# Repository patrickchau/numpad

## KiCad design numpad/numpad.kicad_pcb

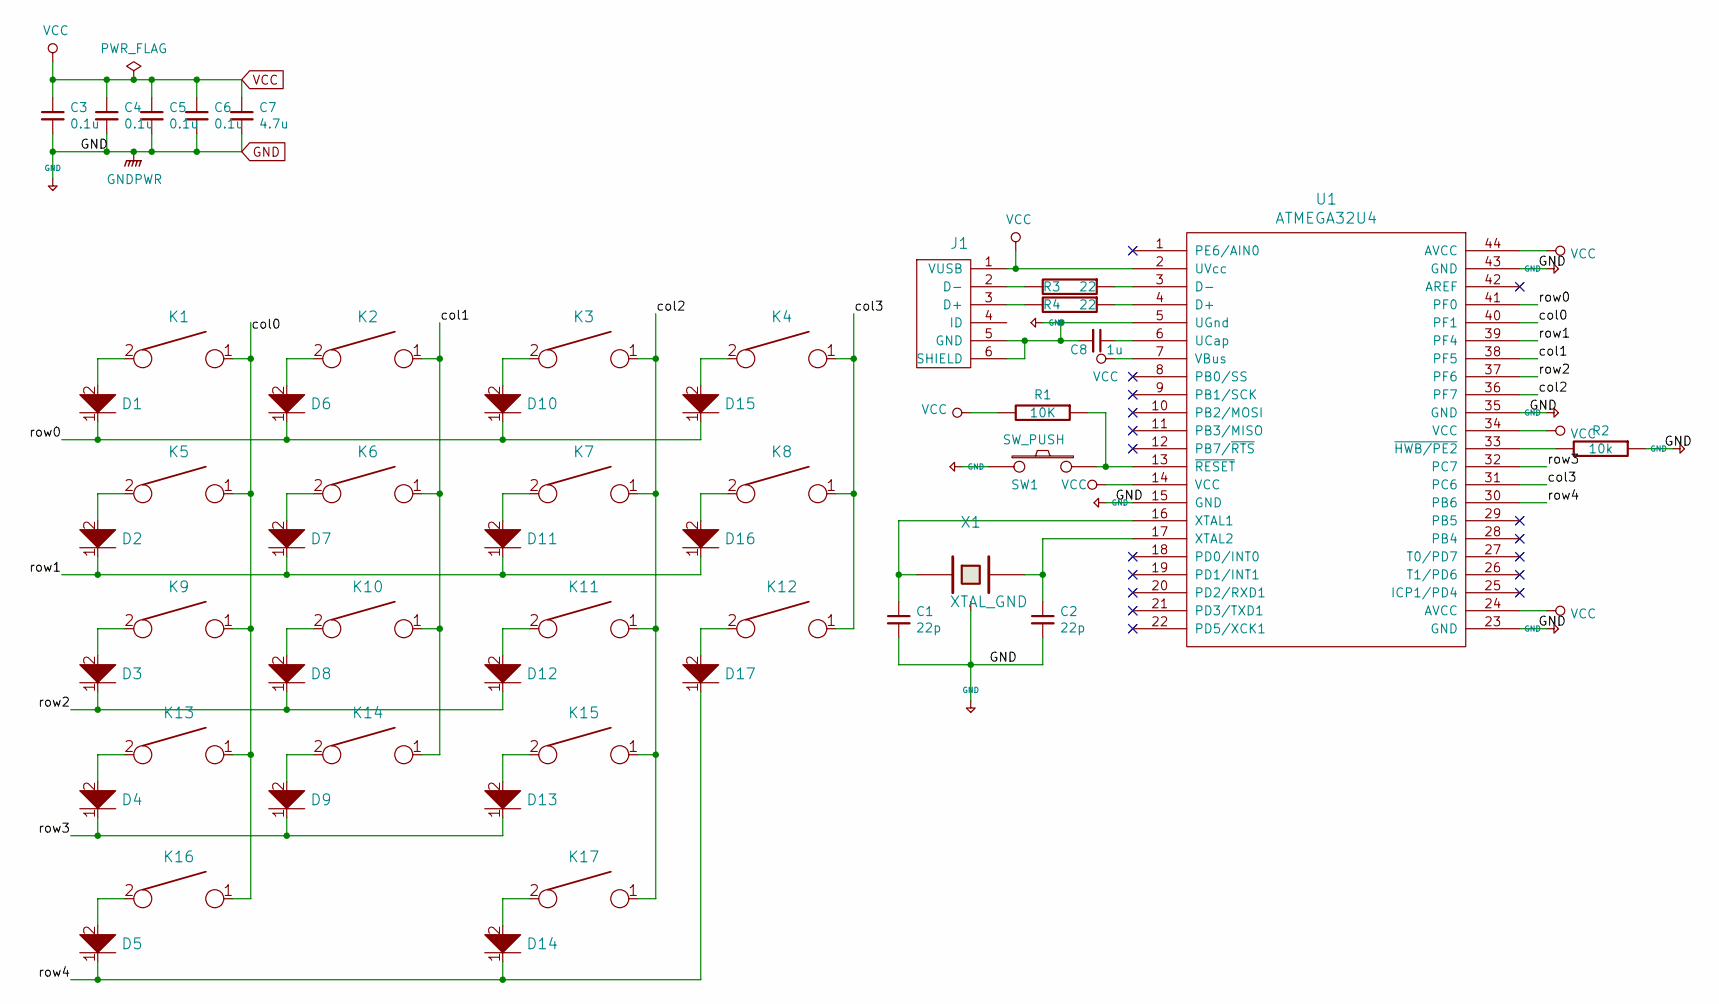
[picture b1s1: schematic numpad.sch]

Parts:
C1, C2: 22p; C_0805_2012Metric_Pad1.15x1.40mm_HandSolder
C3, C4, C5, C6: 0.1u; C_0805_2012Metric_Pad1.15x1.40mm_HandSolder
C7: 4.7u; C_0805_2012Metric_Pad1.15x1.40mm_HandSolder
C8: 1u; C_0805_2012Metric_Pad1.15x1.40mm_HandSolder
D1, D2, D3, D4, D5, D6, D7, D8, D9, D10, D11, D12, D13, D14, D15, D16, D17: D; D_SOD123_axial
J1: USB_mini_micro_B; USB_miniB_hirose_5S8
K1, K2, K3, K4, K5, K6, K7, K8, K9, K10, K11, K12, K13, K14, K15, K16, K17: KEYSW; Mx_Alps_100
R1: 10K; R_0805_2012Metric_Pad1.15x1.40mm_HandSolder
R2: 10k; R_0805_2012Metric_Pad1.15x1.40mm_HandSolder
R3, R4: 22; R_0805_2012Metric_Pad1.15x1.40mm_HandSolder
SW1: SW_PUSH; SW_SPST_TL3342
U1: ATMEGA32U4; TQFP-44_10x10mm_P0.8mm
X1: XTAL_GND; Crystal_SMD_SeikoEpson_FA238-4Pin_3.2x2.5mm_HandSoldering

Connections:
/col0: K1.1, K5.1, K9.1, K13.1, K16.1, U1.40 (PF1)
/col1: K2.1, K6.1, K10.1, K14.1, U1.38 (PF5)
/col2: K3.1, K7.1, K11.1, K15.1, K17.1, U1.36 (PF7)
/col3: K4.1, K8.1, K12.1, U1.31 (PC6)
/row0: D1.1, D6.1, D10.1, D15.1, U1.41 (PF0)
/row1: D2.1, D7.1, D11.1, D16.1, U1.39 (PF4)
/row2: D3.1, D8.1, D12.1, U1.37 (PF6)
/row3: D4.1, D9.1, D13.1, U1.32 (PC7)
/row4: D5.1, D14.1, D17.1, U1.30 (PB6)
GND: C1.2, C2.2, C3.2, C4.2, C5.2, C6.2, C7.2, C8.2, J1.5 (GND), J1.6 (SHIELD), R2.1, SW1.1, U1.5 (UGnd), U1.15 (GND), U1.23 (GND), U1.35 (GND), U1.43 (GND), X1.2 (GND)
unnamed: C1.1, U1.16 (XTAL1), X1.1
unnamed: C2.1, U1.17 (XTAL2), X1.3 (2)
unnamed: C8.1, U1.6 (UCap)
unnamed: D1.2, K1.2
unnamed: D2.2, K5.2
unnamed: D3.2, K9.2
unnamed: D4.2, K13.2
unnamed: D5.2, K16.2
unnamed: D6.2, K2.2
unnamed: D7.2, K6.2
unnamed: D8.2, K10.2
unnamed: D9.2, K14.2
unnamed: D10.2, K3.2
unnamed: D11.2, K7.2
unnamed: D12.2, K11.2
unnamed: D13.2, K15.2
unnamed: D14.2, K17.2
unnamed: D15.2, K4.2
unnamed: D16.2, K8.2
unnamed: D17.2, K12.2
unnamed: J1.2 (D-), R3.2
unnamed: J1.3 (D+), R4.2
unnamed: R1.1, SW1.2, U1.13 (~RESET)
unnamed: R2.2, U1.33 (~HWB/PE2)
unnamed: R3.1, U1.3 (D-)
unnamed: R4.1, U1.4 (D+)
VCC: C3.1, C4.1, C5.1, C6.1, C7.1, J1.1 (VUSB), R1.2, U1.2 (UVcc), U1.7 (VBus), U1.14 (VCC), U1.24 (AVCC), U1.34 (VCC), U1.44 (AVCC)

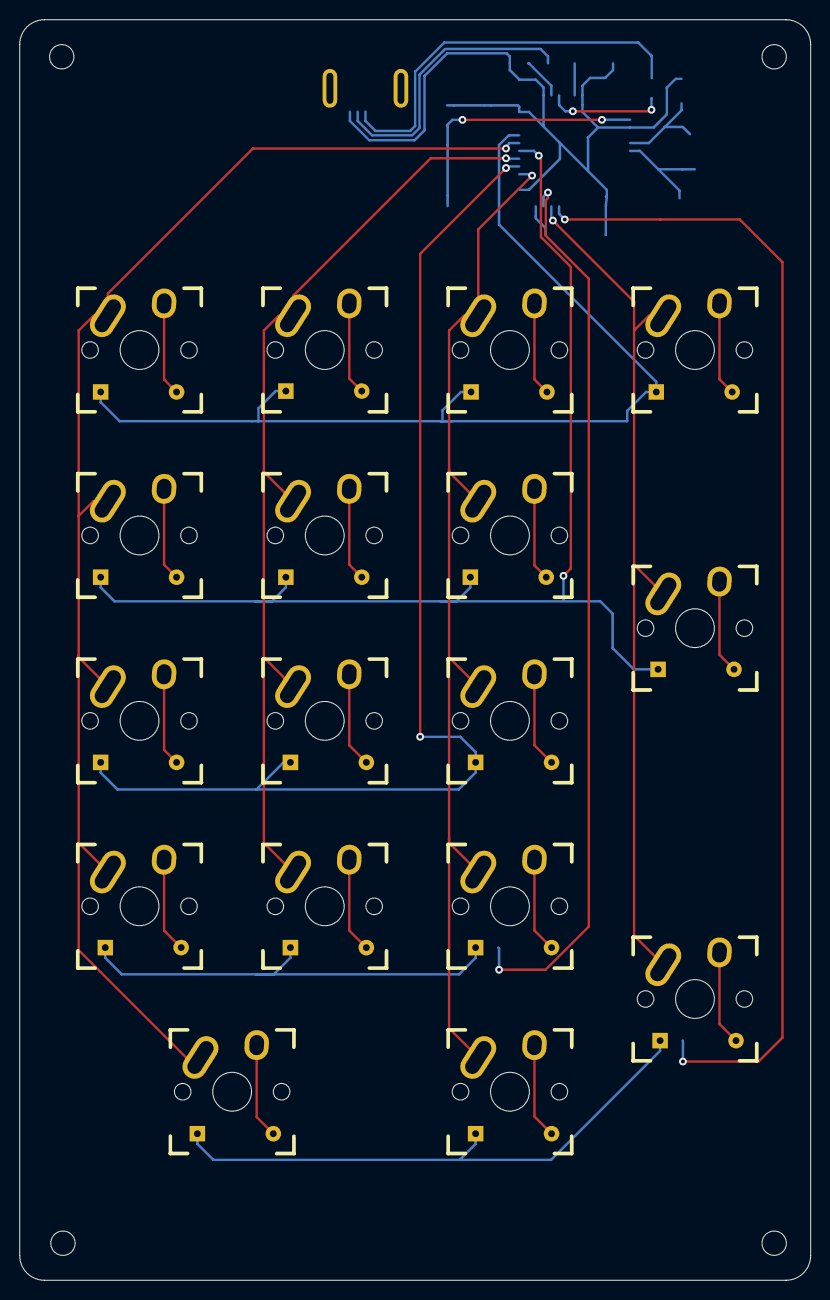
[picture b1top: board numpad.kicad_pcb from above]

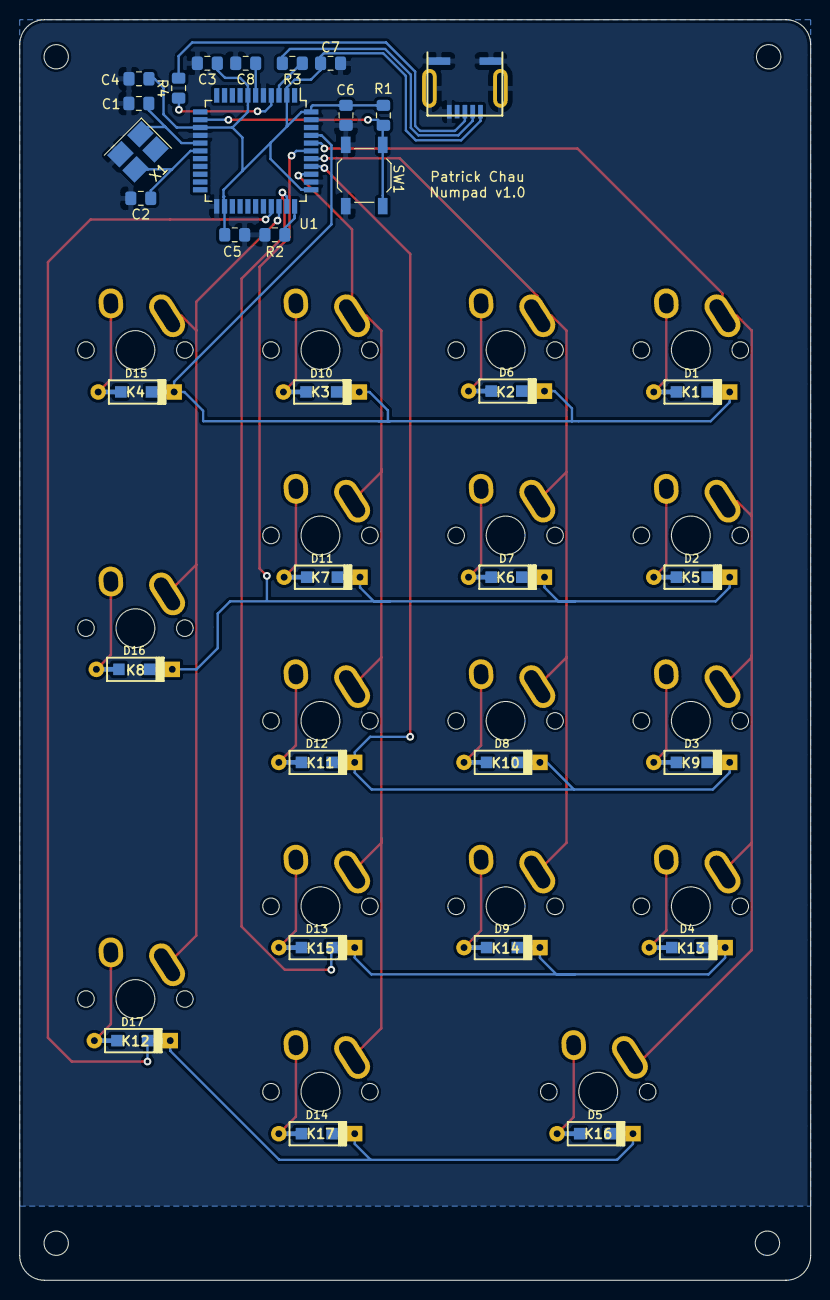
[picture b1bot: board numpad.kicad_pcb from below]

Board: 2 copper layers, 81.3 x 129.5 mm, 50 parts (33 on the bottom side), 37 nets.

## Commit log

2020-06-21 started on the numpad
2020-06-22 finished schematic, associated part to footprints
2020-06-24 finished initial pass on routing
2020-06-24 added mounting holes, exported gerber files for manufacturing
